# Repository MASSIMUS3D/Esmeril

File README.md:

# Esmeril
Projeto de adequação de esmeril para NR12 e uso em instituições educacionais
O projeto visa a adequacao de um Esmeril de uso comum para a NR12, tendo em vista os perigos de uso principalmente no ambiente educacionalç,onde os alunos ainda estao aprendendo o uso correto e ainda estao espostos  a ferimentos graves.

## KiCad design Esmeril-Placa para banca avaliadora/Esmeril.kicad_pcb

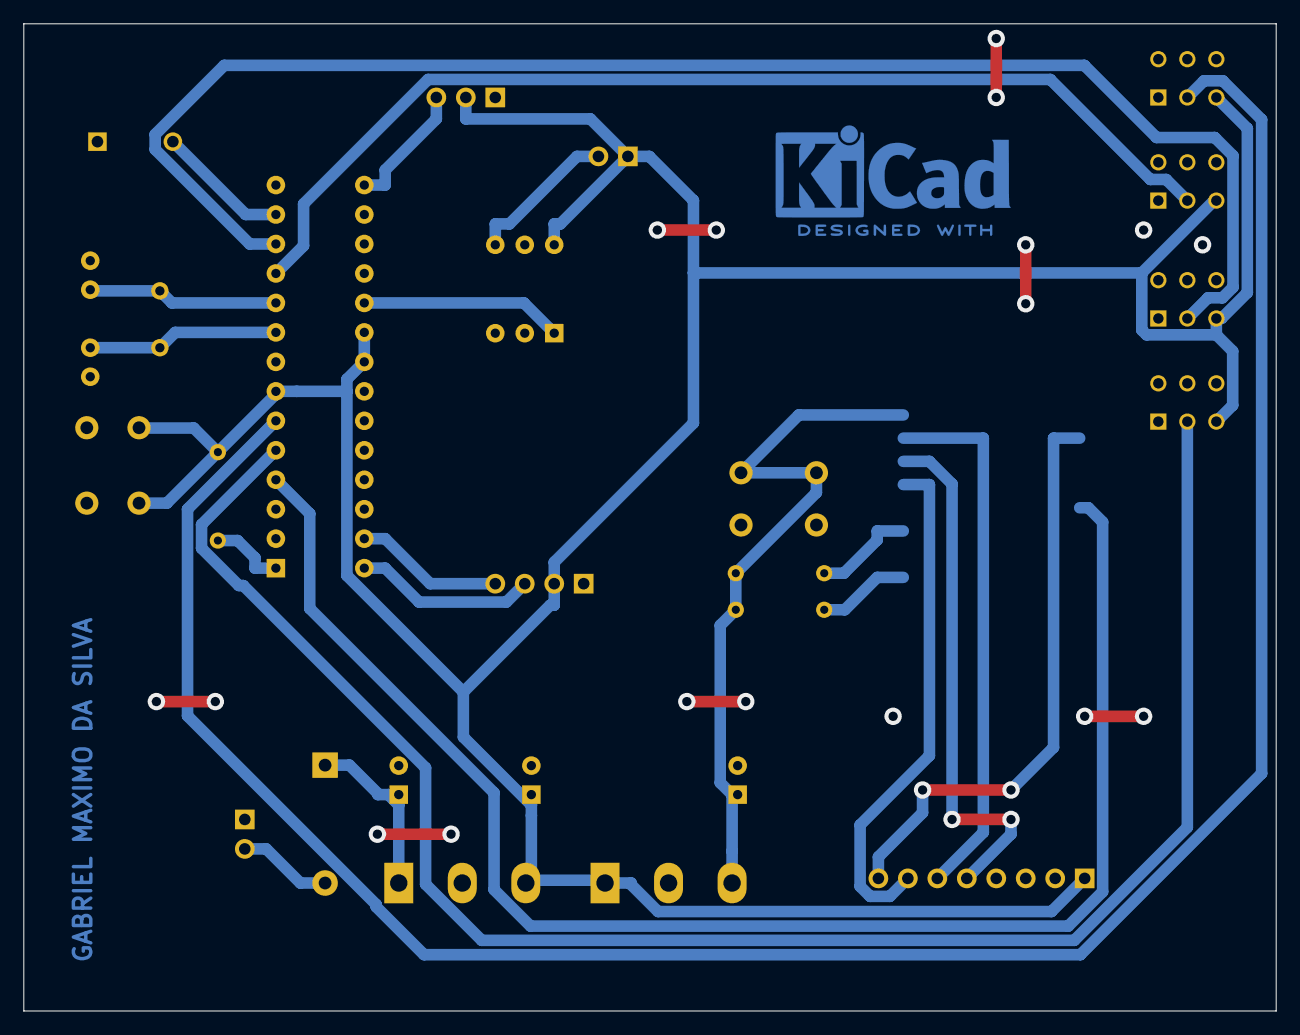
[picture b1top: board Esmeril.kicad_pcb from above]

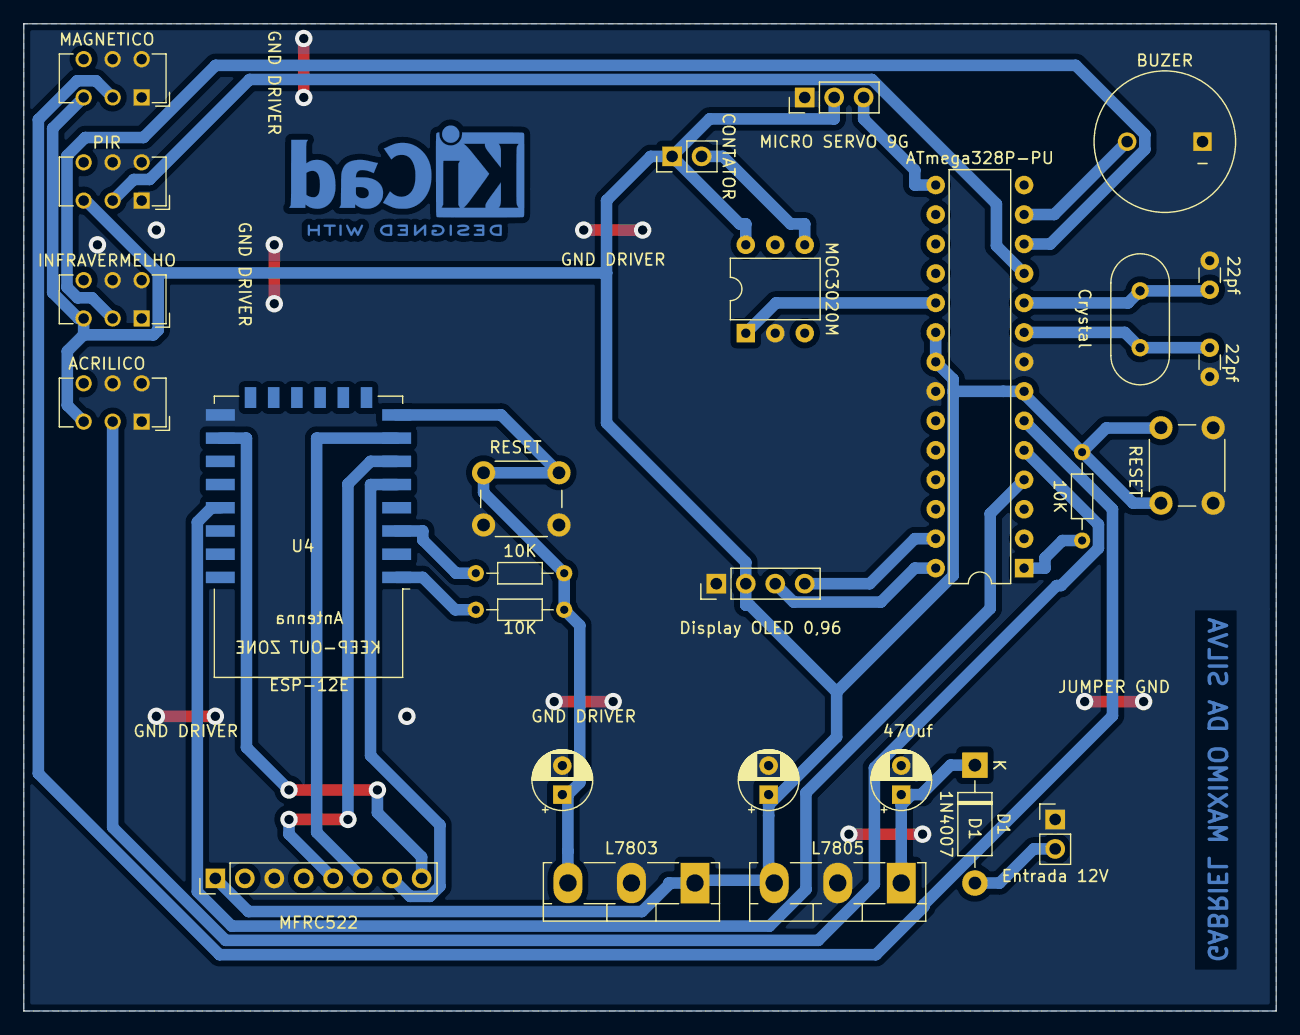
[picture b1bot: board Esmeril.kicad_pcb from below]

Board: 2 copper layers, 108.0 x 85.1 mm, 27 parts (27 on the bottom side), 25 nets.

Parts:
C1: 470uf; CP_Radial_D5.0mm_P2.50mm
C2, C3: 1uf; CP_Radial_D5.0mm_P2.50mm
C4, C5: 22pf; C_Disc_D3.0mm_W1.6mm_P2.50mm
D1: 1N4007; D_DO-41_SOD81_P10.16mm_Horizontal
J1: Entrada 12V; PinHeader_1x02_P2.54mm_Vertical
J2: Display OLED 0,96; PinHeader_1x04_P2.54mm_Vertical
J3: MFRC522; PinHeader_1x08_P2.54mm_Vertical
J4: MICRO SERVO 9G; PinHeader_1x03_P2.54mm_Vertical
J9: BUZER; MagneticBuzzer_ProSignal_ABT-410-RC
J10: CONTATOR; PinHeader_1x02_P2.54mm_Vertical
R1, R2, R3: 10K; R_Axial_DIN0204_L3.6mm_D1.6mm_P7.62mm_Horizontal
SW1, SW2: RESET; SW_PUSH_6mm
SW3: ACRILICO; SW_CuK_JS202011CQN_DPDT_Straight
SW4: INFRAVERMELHO; SW_CuK_JS202011CQN_DPDT_Straight
SW5: PIR; SW_CuK_JS202011CQN_DPDT_Straight
SW6: MAGNETICO; SW_CuK_JS202011CQN_DPDT_Straight
U1: L7805; TO-218-3_Vertical
U2: L7803; TO-218-3_Vertical
U3: MOC3020M; DIP-6_W7.62mm
U4: ESP-12E
U5: ATmega328P-PU; DIP-28_W7.62mm
Y1: Crystal; Crystal_HC18-U_Vertical

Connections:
3,3V: C3.1, R2.1, R3.1, SW2.2, U2.3, U4.8
5V: C2.1, J2.2, J3.1, J4.2, J10.1, R1.1, SW1.2, SW3.3, SW4.3, SW5.3, SW6.3, U1.3, U2.1, U3.6, U5.7, U5.20, U5.21
12V: C1.1, D1.1, U1.1
Acrilico: SW3.2, U5.5
BUZER: J9.2, U5.13
CARTAO: U4.19, U5.4
CONTATOR: U3.1, U5.19
CRISTAL1: C4.1, U5.9, Y1.1
CRISTAL2: C5.1, U5.10, Y1.2
EN-ESP: R3.2, U4.3
GND: C1.2, C2.2, C3.2, C4.2, C5.2, J1.1, J2.1, J3.3, J4.1, J9.1, SW1.1, SW2.1, SW3.1, SW3.4, SW3.5, SW4.1, SW4.4, SW4.5, SW5.1, SW5.4, SW5.5, SW6.1, SW6.4, SW6.5, U1.2, U2.2, U3.2, U4.15, U5.8, U5.22
INFRAVERMELHO: SW4.2, U5.12
MAGNETICO: SW6.2, U5.6
MISO: J3.5, U4.6
MOSI: J3.6, U4.7
unnamed: D1.2, J1.2
unnamed: J10.2, U3.4
PIR: SW5.2, U5.11
RESET: R1.2, U5.1
RESET-ESP: R2.2, U4.1
SCK: J3.7, U4.5
SCL: J2.3, U5.28
SDA: J2.4, U5.27
SERVO: J4.3, U5.15
SS: J3.8, U4.16

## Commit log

2019-11-07 Placa
2019-11-11 Novo
2019-11-11 Atualização
